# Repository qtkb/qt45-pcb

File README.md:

# qt45 keyboard PCB

A single-layout 45-key PCB with a [compatible acrylic layered case](https://github.com/qtkb/qt45-case).

## BOM

| LCSC part # | Description | Package  | Value | Reference | Amount |
|-------------|-------------|----------|------:|-----------|-------:|
| C296091     | Capacitor   | 0805     |  22pF | C1, C2    |      2 |
| C128353     | Capacitor   | 0805     | 0.1uF | C3-C5     |      3 |
| C89854      | Capacitor   | 0805     |  10uF | C6        |      1 |
| C215803     | Capacitor   | 0805     |   1uF | C7        |      1 |
| C2099       | Diode       | SOD-123  |       | D1-D45    |     45 |
| C163512     | Fuse        | 1206     |       | F1        |      1 |
| C325772     | Resistor    | 0805     |    22 | R1, R2    |      2 |
| C103904     | Resistor    | 0805     |   10K | R3, R4    |      2 |
| C92584      | Switch      | SMD      |       |           |      1 |
| C44854      | MCU         | QFP-44   |  32U4 |           |      1 |
| C145778     | Connector   | SMD      |       |           |      1 |
| C255909     | Crystal     | TSX-3225 | 16MHz | Y1        |      1 |

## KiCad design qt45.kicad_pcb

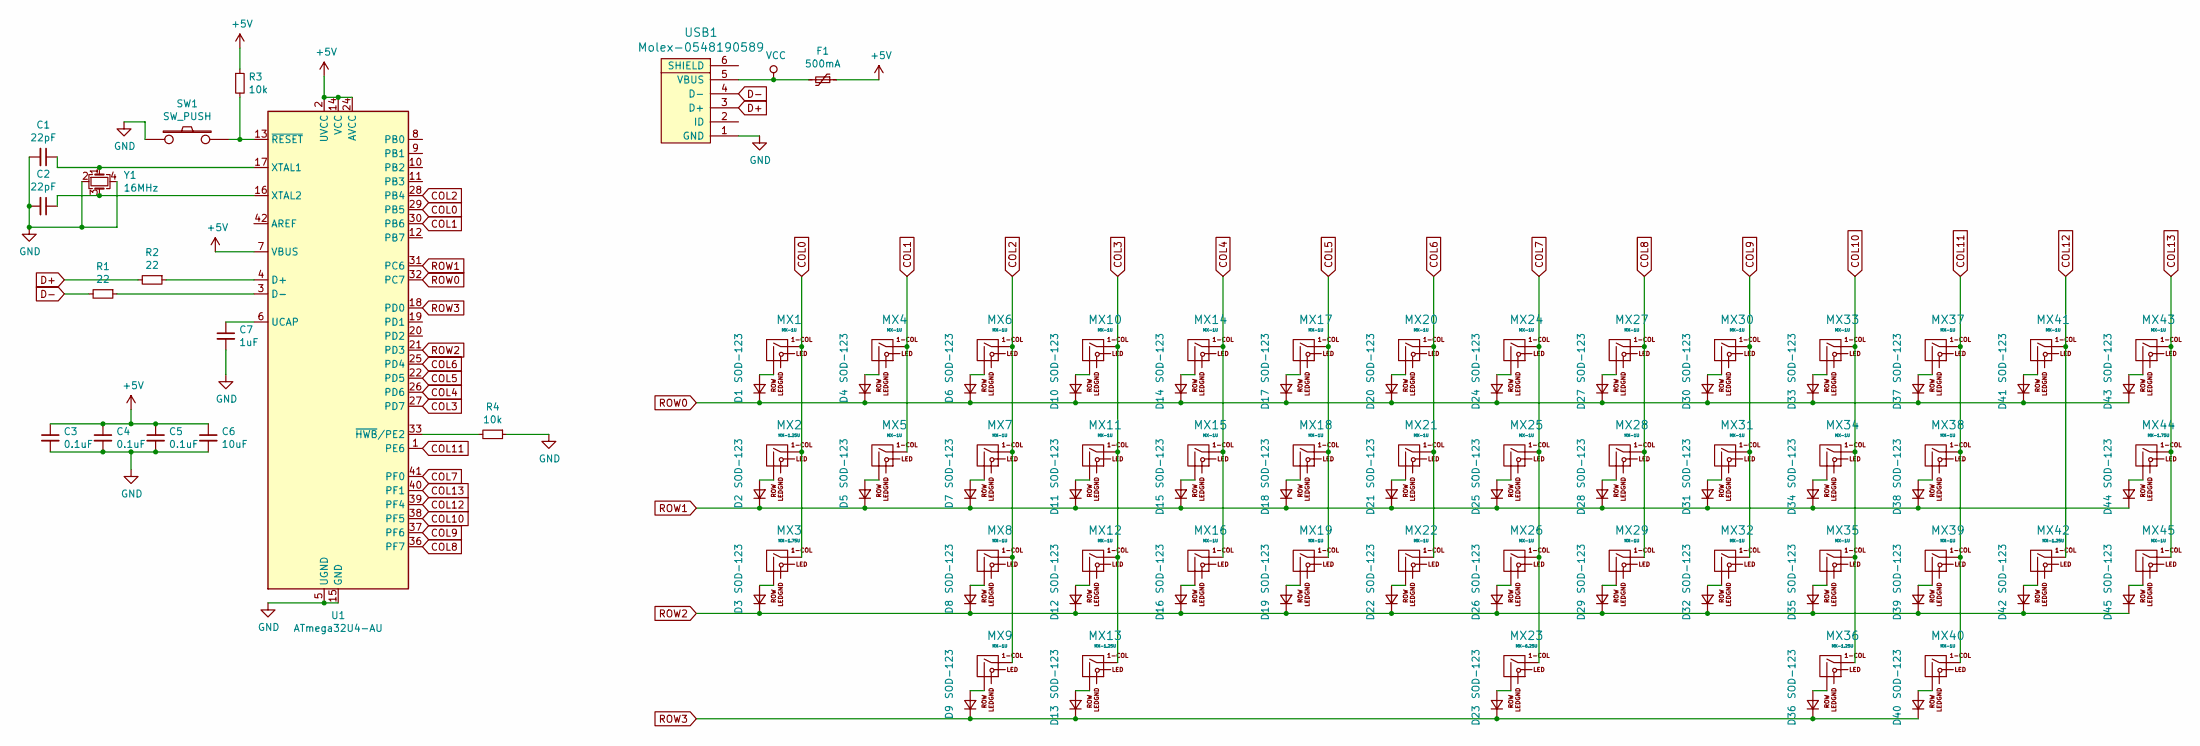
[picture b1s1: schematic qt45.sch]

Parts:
C1, C2: 22pF; C_0805_2012Metric
C3, C4, C5: 0.1uF; C_0805_2012Metric
C6: 10uF; C_0805_2012Metric
C7: 1uF; C_0805_2012Metric
D1, D2, D3, D4, D5, D6, D7, D8, D9, D10, D11, D12, D13, D14, D15, D16, D17, D18, D19, D20, D21, D22, D23, D24, D25, D26, D27, D28, D29, D30, D31, D32, D33, D34, D35, D36, D37, D38, D39, D40, D41, D42, D43, D44, D45: SOD-123; D_SOD-123-Pretty
F1: 500mA; Fuse_1206_3216Metric
MX1, MX4, MX5, MX6, MX7, MX8, MX9, MX10, MX11, MX12, MX14, MX15, MX16, MX17, MX18, MX19, MX20, MX21, MX22, MX24, MX25, MX26, MX27, MX28, MX29, MX30, MX31, MX32, MX33, MX34, MX35, MX37, MX38, MX39, MX40, MX41, MX43, MX45: MX-1U; MXOnly-1U-NoLED
MX2, MX13, MX36, MX42: MX-1.25U; MXOnly-1.25U-NoLED
MX3, MX44: MX-1.75U; MXOnly-1.75U-NoLED
MX23: MX-6.25U; MXOnly-6.25U-ReversedStabilizers-NoLED
R1, R2: 22; R_0805_2012Metric
R3, R4: 10k; R_0805_2012Metric
SW1: SW_PUSH; SKQG-1155865
U1: ATmega32U4-AU; TQFP-44_10x10mm_P0.8mm
USB1: Molex-0548190589
Y1: 16MHz; Crystal_SMD_3225-4Pin_3.2x2.5mm

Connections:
+5V: C3.1, C4.1, C5.1, C6.1, F1.1, R3.1, U1.2 (UVCC), U1.7 (VBUS), U1.14 (VCC), U1.24 (AVCC), U1.34 (VCC), U1.44 (AVCC)
COL0: MX1.1 (COL), MX2.1 (COL), MX3.1 (COL), U1.29 (PB5)
COL1: MX4.1 (COL), MX5.1 (COL), U1.30 (PB6)
COL2: MX6.1 (COL), MX7.1 (COL), MX8.1 (COL), MX9.1 (COL), U1.28 (PB4)
COL3: MX10.1 (COL), MX11.1 (COL), MX12.1 (COL), MX13.1 (COL), U1.27 (PD7)
COL4: MX14.1 (COL), MX15.1 (COL), MX16.1 (COL), U1.26 (PD6)
COL5: MX17.1 (COL), MX18.1 (COL), MX19.1 (COL), U1.22 (PD5)
COL6: MX20.1 (COL), MX21.1 (COL), MX22.1 (COL), U1.25 (PD4)
COL7: MX23.1 (COL), MX24.1 (COL), MX25.1 (COL), MX26.1 (COL), U1.41 (PF0)
COL8: MX27.1 (COL), MX28.1 (COL), MX29.1 (COL), U1.36 (PF7)
COL9: MX30.1 (COL), MX31.1 (COL), MX32.1 (COL), U1.37 (PF6)
COL10: MX33.1 (COL), MX34.1 (COL), MX35.1 (COL), MX36.1 (COL), U1.38 (PF5)
COL11: MX37.1 (COL), MX38.1 (COL), MX39.1 (COL), MX40.1 (COL), U1.1 (PE6)
COL12: MX41.1 (COL), MX42.1 (COL), U1.39 (PF4)
COL13: MX43.1 (COL), MX44.1 (COL), MX45.1 (COL), U1.40 (PF1)
D+: R2.2, USB1.3 (D+)
D-: R1.2, USB1.4 (D-)
GND: C1.2, C2.2, C3.2, C4.2, C5.2, C6.2, C7.2, R4.1, SW1.1, U1.5 (UGND), U1.15 (GND), U1.23 (GND), U1.35 (GND), U1.43 (GND), USB1.1 (GND), Y1.2, Y1.4
unnamed: C1.1, U1.17 (XTAL1), Y1.1
unnamed: C2.1, U1.16 (XTAL2), Y1.3
unnamed: C7.1, U1.6 (UCAP)
unnamed: D1.2 (A), MX1.2 (ROW)
unnamed: D2.2 (A), MX2.2 (ROW)
unnamed: D3.2 (A), MX3.2 (ROW)
unnamed: D4.2 (A), MX4.2 (ROW)
unnamed: D5.2 (A), MX5.2 (ROW)
unnamed: D6.2 (A), MX6.2 (ROW)
unnamed: D7.2 (A), MX7.2 (ROW)
unnamed: D8.2 (A), MX8.2 (ROW)
unnamed: D9.2 (A), MX9.2 (ROW)
unnamed: D10.2 (A), MX10.2 (ROW)
unnamed: D11.2 (A), MX11.2 (ROW)
unnamed: D12.2 (A), MX12.2 (ROW)
unnamed: D13.2 (A), MX13.2 (ROW)
unnamed: D14.2 (A), MX14.2 (ROW)
unnamed: D15.2 (A), MX15.2 (ROW)
unnamed: D16.2 (A), MX16.2 (ROW)
unnamed: D17.2 (A), MX17.2 (ROW)
unnamed: D18.2 (A), MX18.2 (ROW)
unnamed: D19.2 (A), MX19.2 (ROW)
unnamed: D20.2 (A), MX20.2 (ROW)
unnamed: D21.2 (A), MX21.2 (ROW)
unnamed: D22.2 (A), MX22.2 (ROW)
unnamed: D23.2 (A), MX23.2 (ROW)
unnamed: D24.2 (A), MX24.2 (ROW)
unnamed: D25.2 (A), MX25.2 (ROW)
unnamed: D26.2 (A), MX26.2 (ROW)
unnamed: D27.2 (A), MX27.2 (ROW)
unnamed: D28.2 (A), MX28.2 (ROW)
unnamed: D29.2 (A), MX29.2 (ROW)
unnamed: D30.2 (A), MX30.2 (ROW)
unnamed: D31.2 (A), MX31.2 (ROW)
unnamed: D32.2 (A), MX32.2 (ROW)
unnamed: D33.2 (A), MX33.2 (ROW)
unnamed: D34.2 (A), MX34.2 (ROW)
unnamed: D35.2 (A), MX35.2 (ROW)
unnamed: D36.2 (A), MX36.2 (ROW)
unnamed: D37.2 (A), MX37.2 (ROW)
unnamed: D38.2 (A), MX38.2 (ROW)
unnamed: D39.2 (A), MX39.2 (ROW)
unnamed: D40.2 (A), MX40.2 (ROW)
unnamed: D41.2 (A), MX41.2 (ROW)
unnamed: D42.2 (A), MX42.2 (ROW)
unnamed: D43.2 (A), MX43.2 (ROW)
unnamed: D44.2 (A), MX44.2 (ROW)
unnamed: D45.2 (A), MX45.2 (ROW)
unnamed: R1.1, U1.3 (D-)
unnamed: R2.1, U1.4 (D+)
unnamed: R3.2, SW1.2, U1.13 (~RESET)
unnamed: R4.2, U1.33 (~HWB~/PE2)
ROW0: D1.1 (K), D4.1 (K), D6.1 (K), D10.1 (K), D14.1 (K), D17.1 (K), D20.1 (K), D24.1 (K), D27.1 (K), D30.1 (K), D33.1 (K), D37.1 (K), D41.1 (K), D43.1 (K), U1.32 (PC7)
ROW1: D2.1 (K), D5.1 (K), D7.1 (K), D11.1 (K), D15.1 (K), D18.1 (K), D21.1 (K), D25.1 (K), D28.1 (K), D31.1 (K), D34.1 (K), D38.1 (K), D44.1 (K), U1.31 (PC6)
ROW2: D3.1 (K), D8.1 (K), D12.1 (K), D16.1 (K), D19.1 (K), D22.1 (K), D26.1 (K), D29.1 (K), D32.1 (K), D35.1 (K), D39.1 (K), D42.1 (K), D45.1 (K), U1.21 (PD3)
ROW3: D9.1 (K), D13.1 (K), D23.1 (K), D36.1 (K), D40.1 (K), U1.18 (PD0)
VCC: F1.2, USB1.5 (VBUS)

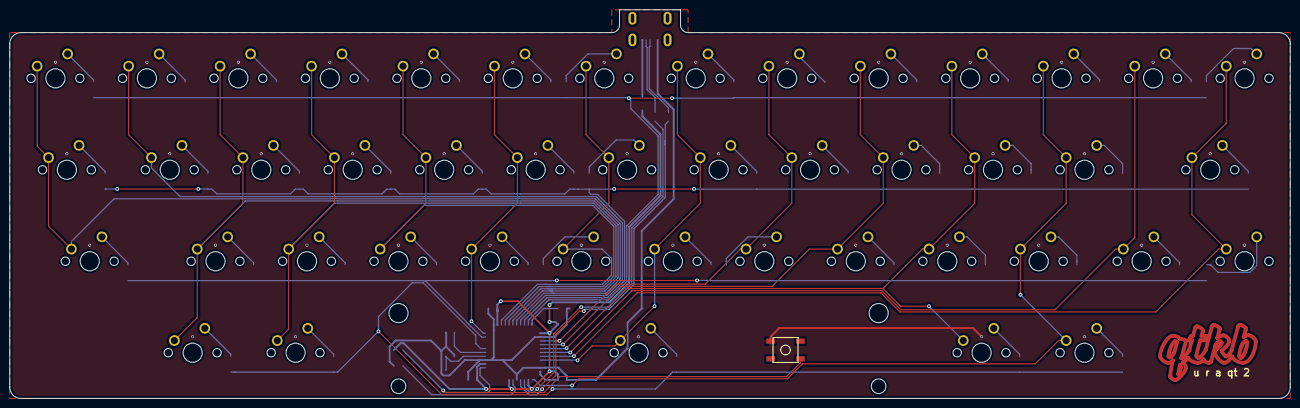
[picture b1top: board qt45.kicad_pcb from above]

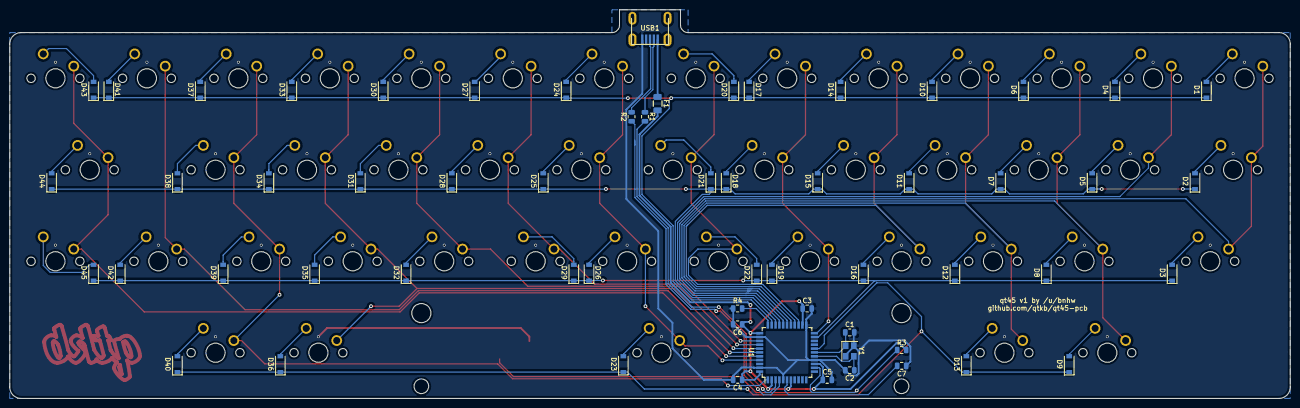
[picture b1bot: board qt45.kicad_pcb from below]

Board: 2 copper layers, 266.7 x 81.0 mm, 106 parts (60 on the bottom side), 75 nets.

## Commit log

2019-03-26 Create project
2019-03-26 Add symbol libraries
2019-03-26 Draw schematic
2019-03-26 Generate netlist
2019-03-26 Layout key switches
2019-03-27 Rough placement of components
2019-03-27 Route key switches
2019-03-27 Routing (no rows and columns)
2019-03-27 Routing fixes
2019-03-27 Start reroute
2019-03-28 More routing
2019-03-28 First draft of routing
2019-03-28 Add .gitignore
2019-03-28 Add license
2019-03-28 Add ground plane
2019-03-28 Re-route to maximise ground plane
2019-03-28 Warning about this being pre-release
2019-03-28 Config for export
2019-03-30 Create BOM
2019-03-30 Add branding and adjust silkscreen
2019-03-30 Fix some issues
2019-03-30 Increase size of copper in logo and add version number
2019-03-31 Add connector to BOM
2019-04-01 Update README formatting
2019-04-17 Choose a diode that will actually fit the pads (whoops)
2019-05-18 Update license
2019-05-18 Reformat BOM and include references
2019-05-18 Swap out image on README
2019-07-28 Add front ground plane
